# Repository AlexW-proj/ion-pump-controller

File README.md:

# ion-pump-controller
open source controller that takes 24V in and spits out 0 - 7000V, set by a knob with an adjustable ramp time. still just theoretical design, not tested physically

IMPORTANT: in the schematic, there is no output! Ion pumps may have a few different input types and I dont know what they are, so you must insert your own! in the bottom left of the schematic, look for "final Vout", and put your desired output connector across it!

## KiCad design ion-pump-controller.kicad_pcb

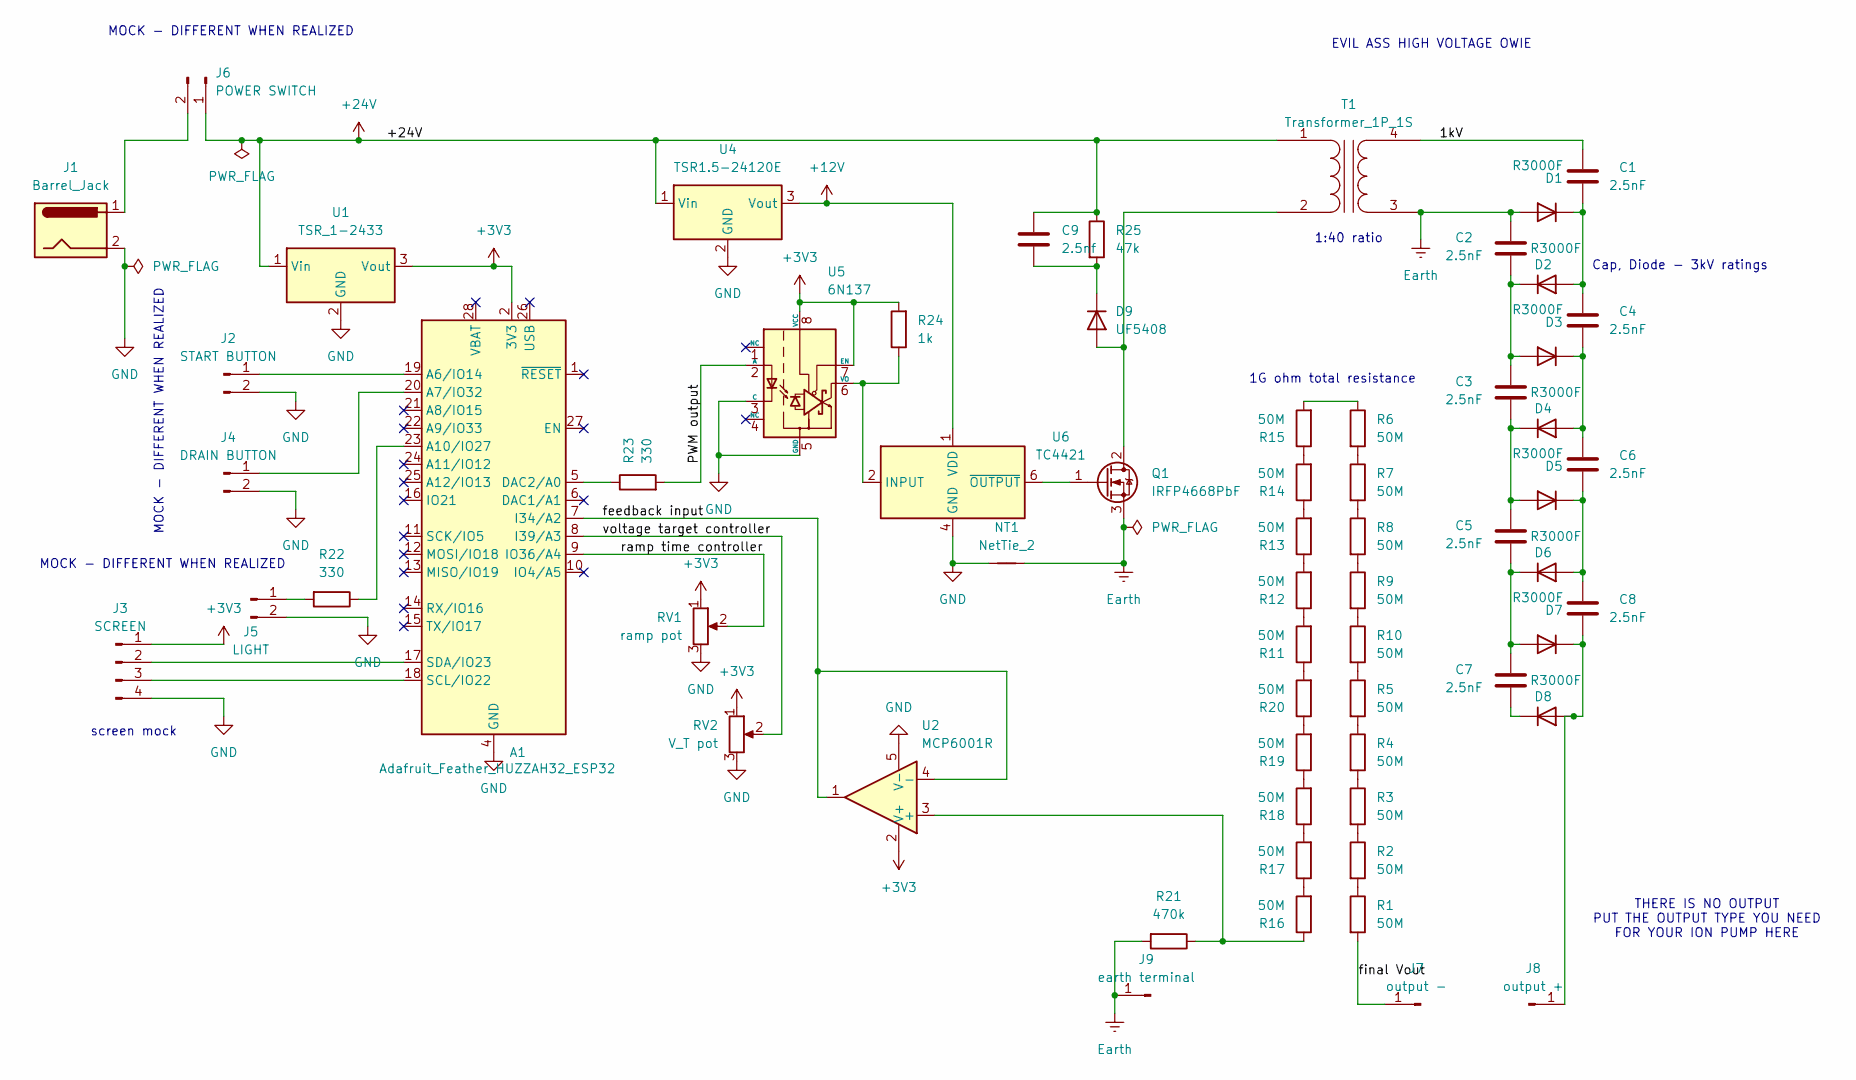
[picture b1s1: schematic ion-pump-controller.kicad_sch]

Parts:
A1: Adafruit_Feather_HUZZAH32_ESP32; Adafruit_Feather
C1, C2, C3, C4, C5, C6, C7, C8: 2.5nF; C_Disc_D14.5mm_W5.0mm_P10.00mm
C9: 2.5nf; C_Disc_D14.5mm_W5.0mm_P10.00mm
D1, D2, D3, D4, D5, D6, D7, D8: R3000F; D_T-1_P12.70mm_Horizontal
D9: UF5408; D_DO-201AD_P15.24mm_Horizontal
J1: Barrel_Jack; BarrelJack_SwitchcraftConxall_RAPC10U_Horizontal
J2: START BUTTON; TerminalBlock_Phoenix_MKDS-1,5-2_1x02_P5.00mm_Horizontal
J3: SCREEN; PhoenixContact_SPT_2.5_4-H-5.0_1x04_P5.0mm_Horizontal
J4: DRAIN BUTTON; TerminalBlock_Phoenix_MKDS-1,5-2_1x02_P5.00mm_Horizontal
J5: LIGHT; TerminalBlock_Phoenix_MKDS-1,5-2_1x02_P5.00mm_Horizontal
J6: POWER SWITCH; TerminalBlock_Phoenix_MKDS-1,5-2_1x02_P5.00mm_Horizontal
J7: output -; TestPoint_Pad_4.0x4.0mm
J8: output +; TestPoint_Pad_4.0x4.0mm
J9: earth terminal; TestPoint_Pad_4.0x4.0mm
NT1: NetTie_2; NetTie-2_SMD_Pad2.0mm
Q1: IRFP4668PbF; TO-247-3_Vertical
R1, R2, R3, R4, R5, R6, R7, R8, R9, R10, R11, R12, R13, R14, R15, R16, R17, R18, R19, R20: 50M; R_Axial_DIN0207_L6.3mm_D2.5mm_P10.16mm_Horizontal
R21: 470k; R_Axial_DIN0411_L9.9mm_D3.6mm_P25.40mm_Horizontal
R22, R23: 330; R_Axial_DIN0411_L9.9mm_D3.6mm_P25.40mm_Horizontal
R24: 1k; R_Axial_DIN0411_L9.9mm_D3.6mm_P25.40mm_Horizontal
R25: 47k; R_Axial_DIN0411_L9.9mm_D3.6mm_P25.40mm_Horizontal
RV1: ramp pot; Potentiometer_ACP_CA6-H2,5_Horizontal
RV2: V_T pot; Potentiometer_ACP_CA6-H2,5_Horizontal
T1: Transformer_1P_1S; TerminalBlock_MaiXu_MX126-5.0-04P_1x04_P5.00mm
U1: TSR_1-2433; Converter_DCDC_TRACO_TSR-1_THT
U2: MCP6001R; SOT-23-5
U4: TSR1.5-24120E; Converter_DCDC_TRACO_TSR1.5-24xxE_24120E_THT
U5: 6N137; DIP-8_W7.62mm
U6: TC4421; DIP-8_W7.62mm

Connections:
+3V3: A1.2 (3V3), J3.1, R24.2, RV1.1, RV2.1, U1.3 (Vout), U2.2 (V+), U5.7 (EN), U5.8 (VCC)
+12V: U4.3 (Vout), U6.1 (VDD), U6.8 (VDD)
+24V: C9.1, J6.1, R25.1, T1.1 (AA), U1.1 (Vin), U4.1 (Vin)
/1kV: C1.2, T1.4 (SB)
/PWM output: R23.2, U5.2 (A)
/feedback input: A1.7 (I34/A2), U2.1, U2.4 (-)
/final Vout: J7.1, R1.2
/ramp time controller: A1.9 (IO36/A4), RV1.2
/voltage target controller: A1.8 (I39/A3), RV2.2
Earth: C2.2, D1.2 (A), J9.1, NT1.2, Q1.3 (S), R21.2, T1.3 (SA)
GND: A1.4 (GND), J1.2, J2.2, J3.4, J4.2, J5.2, NT1.1, RV1.3, RV2.3, U1.2 (GND), U2.5 (V-), U4.2 (GND), U5.3 (C), U5.5 (GND), U6.4 (GND), U6.5 (GND)
unnamed: A1.19 (A6/IO14), J2.1
unnamed: A1.20 (A7/IO32), J4.1
unnamed: A1.23 (A10/IO27), R22.1
unnamed: A1.5 (DAC2/A0), R23.1
unnamed: A1.18 (SCL/IO22), J3.3
unnamed: A1.17 (SDA/IO23), J3.2
unnamed: C1.1, C4.2, D1.1 (K), D2.2 (A)
unnamed: C2.1, C3.2, D2.1 (K), D3.2 (A)
unnamed: C4.1, C6.2, D3.1 (K), D4.2 (A)
unnamed: C3.1, C5.2, D4.1 (K), D5.2 (A)
unnamed: C6.1, C8.2, D5.1 (K), D6.2 (A)
unnamed: C5.1, C7.2, D6.1 (K), D7.2 (A)
unnamed: C8.1, D7.1 (K), D8.2 (A), J8.1
unnamed: C7.1, D8.1 (K)
unnamed: D9.2 (A), Q1.2 (D), T1.2 (AB)
unnamed: C9.2, D9.1 (K), R25.2
unnamed: J5.1, R22.2
unnamed: J1.1, J6.2
unnamed: Q1.1 (G), U6.6 (~OUTPUT), U6.7 (~OUTPUT)
unnamed: R1.1, R2.2
unnamed: R2.1, R3.2
unnamed: R3.1, R4.2
unnamed: R4.1, R5.2
unnamed: R6.2, R7.1
unnamed: R7.2, R8.1
unnamed: R8.2, R9.1
unnamed: R9.2, R10.1
unnamed: R5.1, R10.2
unnamed: R11.1, R20.2
unnamed: R11.2, R12.1
unnamed: R12.2, R13.1
unnamed: R13.2, R14.1
unnamed: R14.2, R15.1
unnamed: R6.1, R15.2
unnamed: R16.2, R17.1
unnamed: R17.2, R18.1
unnamed: R18.2, R19.1
unnamed: R19.2, R20.1
unnamed: R16.1, R21.1, U2.3 (+)
unnamed: R24.1, U5.6 (VO), U6.2 (INPUT)

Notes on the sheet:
MOCK - DIFFERENT WHEN REALIZED
Cap, Diode - 3kV ratings
screen mock
1G ohm total resistance
THERE IS NO OUTPUT PUT THE OUTPUT TYPE YOU NEED FOR YOUR ION PUMP HERE
1:40 ratio
EVIL ASS HIGH VOLTAGE OWIE

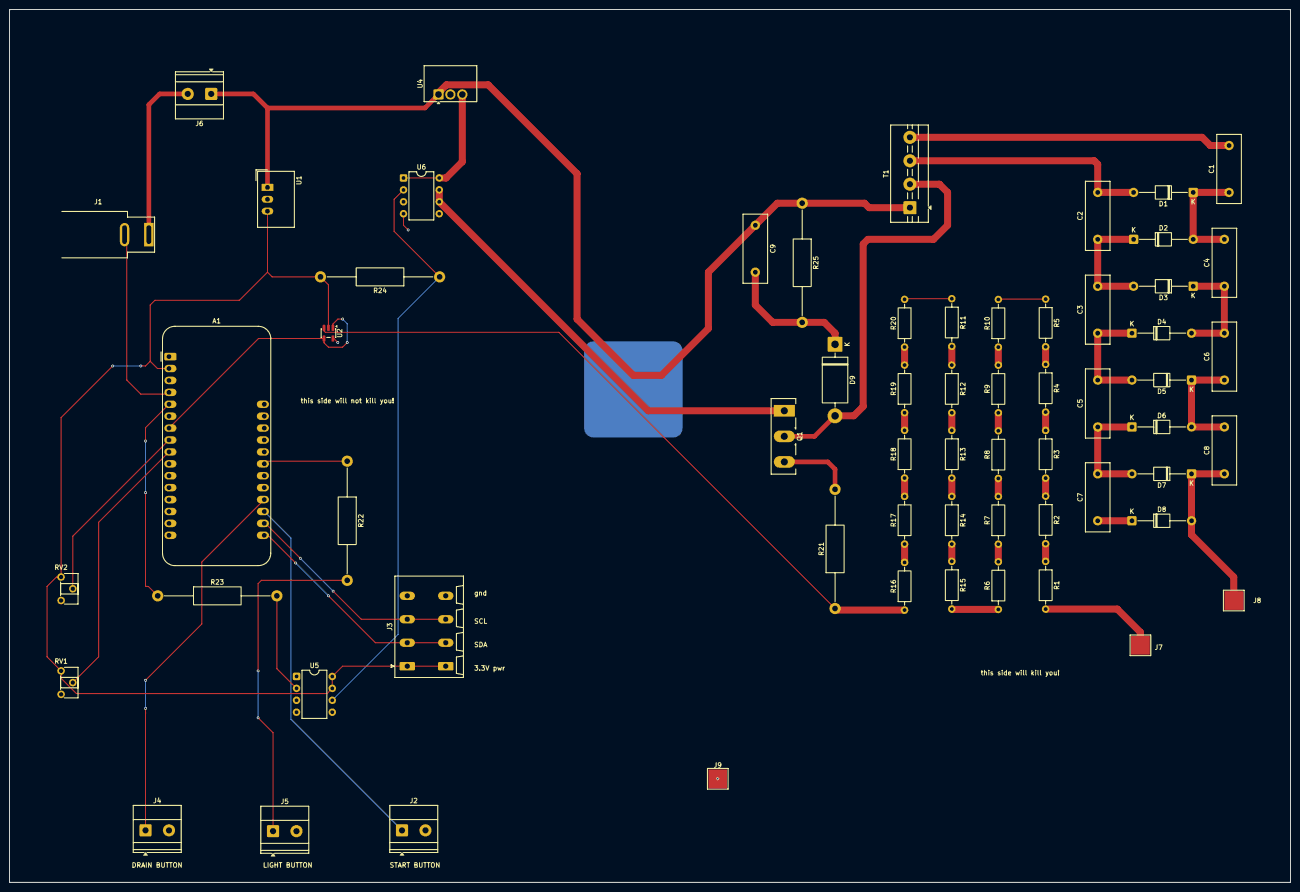
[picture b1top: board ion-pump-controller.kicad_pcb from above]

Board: 2 copper layers, 273.1 x 186.1 mm, 63 parts (1 on the bottom side), 51 nets.

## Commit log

2026-04-06 v1.0
    theoretically works, untested physically
2026-04-06 KiKad files
    unfinished, just getting these in here
2026-04-16 1.0 version
    these are the new schematic and pcb files for what should be the theoretically working board
2026-04-22 v1.1
    split the ground plane to high and low voltage, made the output two pads instead of screw terminals
2026-04-22 v1.1
2026-04-22 v1.1
    added a pad for earth gnd
